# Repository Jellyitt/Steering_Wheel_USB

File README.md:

# Steering Wheel USB

This repository holds the code and electronics for a USB based steering wheel rim with a dual clutch system. These are used in both this [Formula style rim](https://www.thingiverse.com/thing:4923454) and this [G29 button box mod](https://www.thingiverse.com/).

This is intended to be used with the Arduino Pro Mirco Board. Using the breakout PCB isn't necessary but steering wheels with larger button/switch counts will get messy very quick using the button matix method that the program utilises. If using a different wiring configuration to that of the PCB, insure that all the input pin assignments are changed acordingly. The current wiring is displayed in the figure below. Com1-6 lines are treaded as signal lines to one of the switches/buttons in each group and then each group of switches/buttons has a single common line that connects them all together. This makes up a matrix of buttons/switches, theres a number of guides online that explain it better and have pretty pictures and I would advise you go have a look for yourself. 

The dual clutch system allows for on the fly adjustment of the slave clutch. The clutch adjustment mode can be actived by two buttons held simultaneously or a long hold of a single button. The clutch adjustment can be fine tuned with an adjustable increment (i.e. adjust at ±1% or ±0.1 etc). The buttons used to perform the clutch adjustment can be customised. The clutches will need to have their ranges calculated to be accuate but a program is include with instructions in the code.   

No further devolopment will be done on this version.

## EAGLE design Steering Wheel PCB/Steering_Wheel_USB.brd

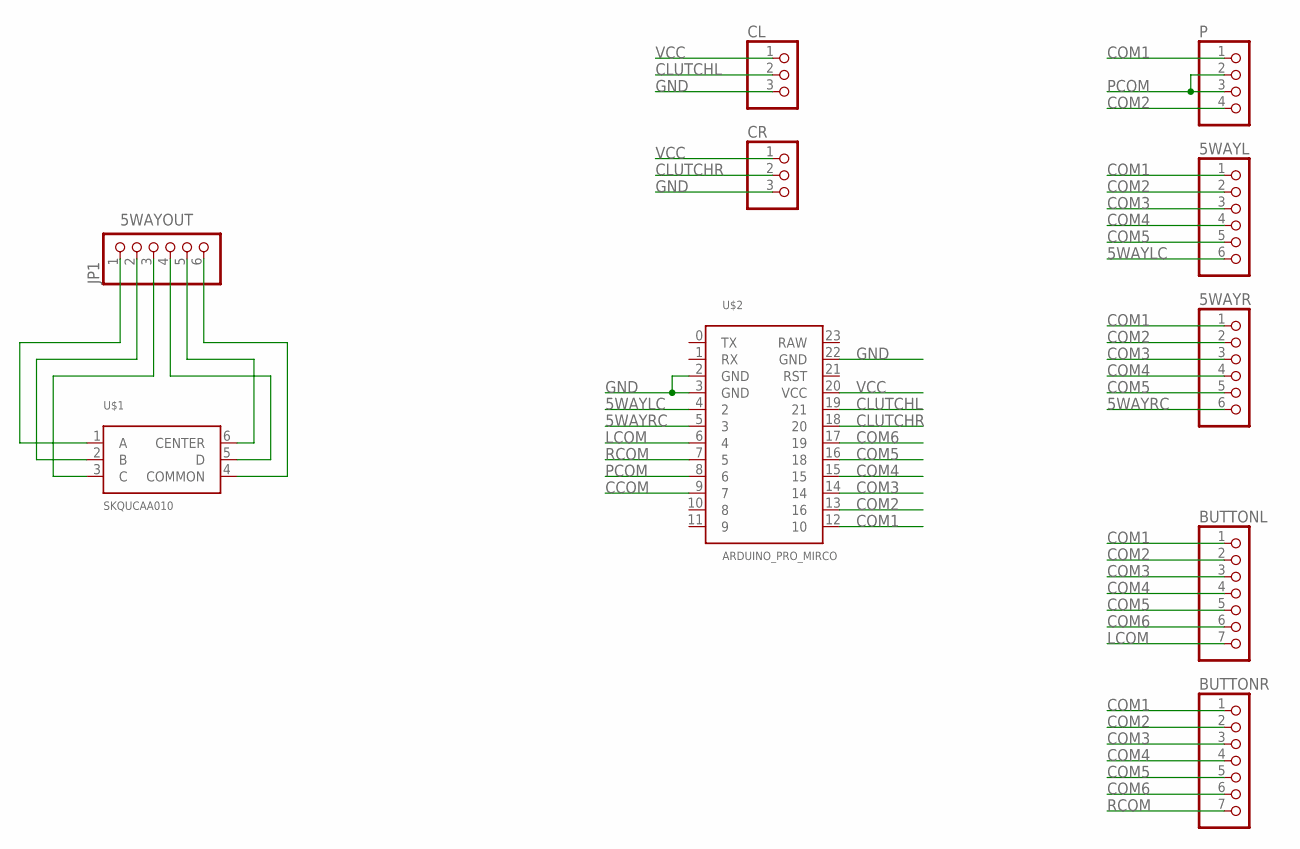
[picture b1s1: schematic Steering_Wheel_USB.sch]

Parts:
5WAYL, 5WAYR: PINHD-1X6; 1X06
BUTTONL: PINHD-1X7; 1X07
BUTTONR: PINHD-1X7; 1X07
CL: PINHD-1X3; 1X03
CR: PINHD-1X3; 1X03
JP1: PINHD-1X6; 1X06
P: PINHD-1X4; 1X04
U$1: SKQUCAA010
U$2: ARDUINO_PRO_MIRCO; ARDUINO_PRO_MICRO

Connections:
5WAYLC: 5WAYL.6, U$2.4 (2)
5WAYOUT: JP1.1, U$1.1 (A)
5WAYRC: 5WAYR.6, U$2.5 (3)
CCOM: U$2.9 (7)
CLUTCHL: CL.2, U$2.19 (21)
CLUTCHR: CR.2, U$2.18 (20)
COM1: 5WAYL.1, 5WAYR.1, BUTTONL.1, BUTTONR.1, P.1, U$2.12 (10)
COM2: 5WAYL.2, 5WAYR.2, BUTTONL.2, BUTTONR.2, P.4, U$2.13 (16)
COM3: 5WAYL.3, 5WAYR.3, BUTTONL.3, BUTTONR.3, U$2.14
COM4: 5WAYL.4, 5WAYR.4, BUTTONL.4, BUTTONR.4, U$2.15
COM5: 5WAYL.5, 5WAYR.5, BUTTONL.5, BUTTONR.5, U$2.16 (18)
COM6: BUTTONL.6, BUTTONR.6, U$2.17 (19)
GND: CL.3, CR.3, U$2.2 (GND), U$2.3 (GND), U$2.22 (GND)
LCOM: BUTTONL.7, U$2.6 (4)
unnamed: JP1.2, U$1.2 (B)
unnamed: JP1.3, U$1.3 (C)
unnamed: JP1.4, U$1.5 (D)
unnamed: JP1.5, U$1.6 (CENTER)
unnamed: JP1.6, U$1.4 (COMMON)
PCOM: P.2, P.3, U$2.8 (6)
RCOM: BUTTONR.7, U$2.7 (5)
VCC: CL.1, CR.1, U$2.20 (VCC)

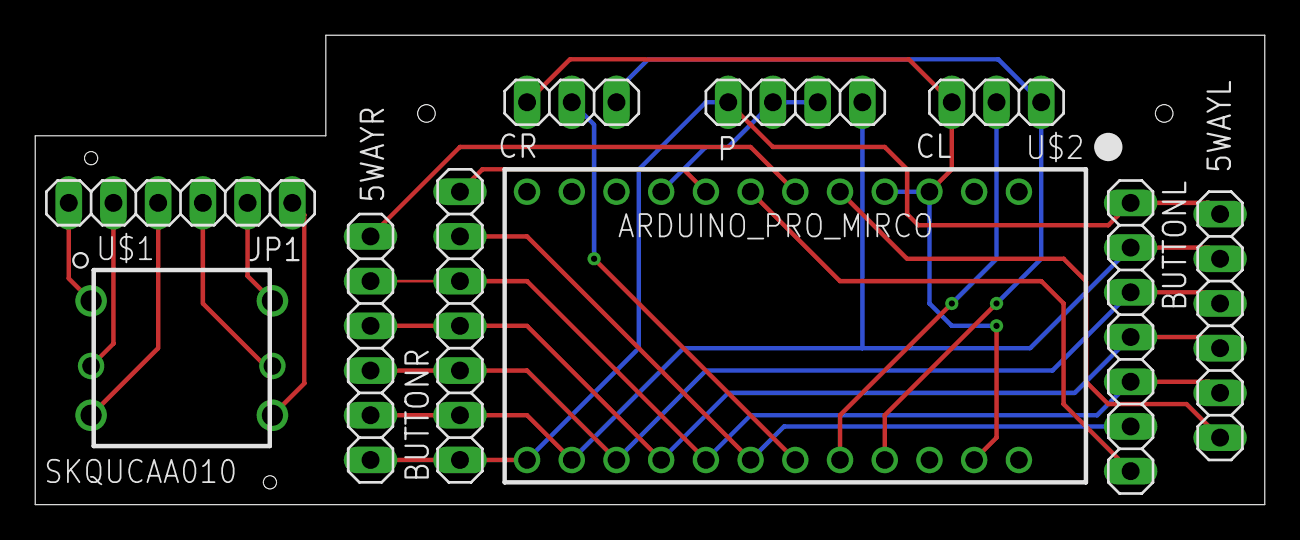
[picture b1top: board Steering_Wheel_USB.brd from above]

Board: 2 copper layers, 69.8 x 26.7 mm, 10 parts (0 on the bottom side), 21 nets.

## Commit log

2021-08-03 added electronics pinout
2021-08-03 adding matrix electronics stuff
2021-08-03 added extra diagram
2021-08-03 added extra diagram
    (hopefully correct file this time)
2021-08-03 wrong file
2021-08-03 right file
2021-08-03 right file try 2
2021-08-03 update image link
2021-08-03 updated link
